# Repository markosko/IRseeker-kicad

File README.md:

View this project on [CADLAB.io](https://cadlab.io/project/27377).

# IRseeker-kicad

Used as replacement for IRseeker sensor and similar for Lightweight / Entry leagues with infra ball in Robocup Junior, based on STM32G431CBU6 and TSSP4038

With communication over I2C or Serial protocol.

Serial over **TX_3V** / **RX_3V** pins is **only 3.3V tolerant**!

Serial over **TX3_5V** / **RX3_5V** pins is **5V tolerant**.

**I2C** is 5V tolerant.

Logic **AND** gates **HEF4082BT** at **U2** and **U4** are optional for chip at PC6 pin input to detect if any TSSP4038 detects ball.

**AMS1117** part is not needed in case of powering from 3.3V source

Programmed by external STLINK or similar over SWD pins at J13 header.

[Basic serial code](https://github.com/markosko/IRseeker-stmduino-serial)

[Basic I2C code](https://github.com/markosko/IRseeker-stmduino-i2c)

# 3D view from KiCad

# Assembled images

# Sponsored by

<p align=center>
A big thanks to <a href="https://www.pcbway.com/">PCBway</a> for sponsoring my project! Their rapid-prototyping services provided top-quality PCB boards, streamlining the entire process from order to delivery. I was particularly impressed by their outstanding customer support, which was willing to change few details.
</p>

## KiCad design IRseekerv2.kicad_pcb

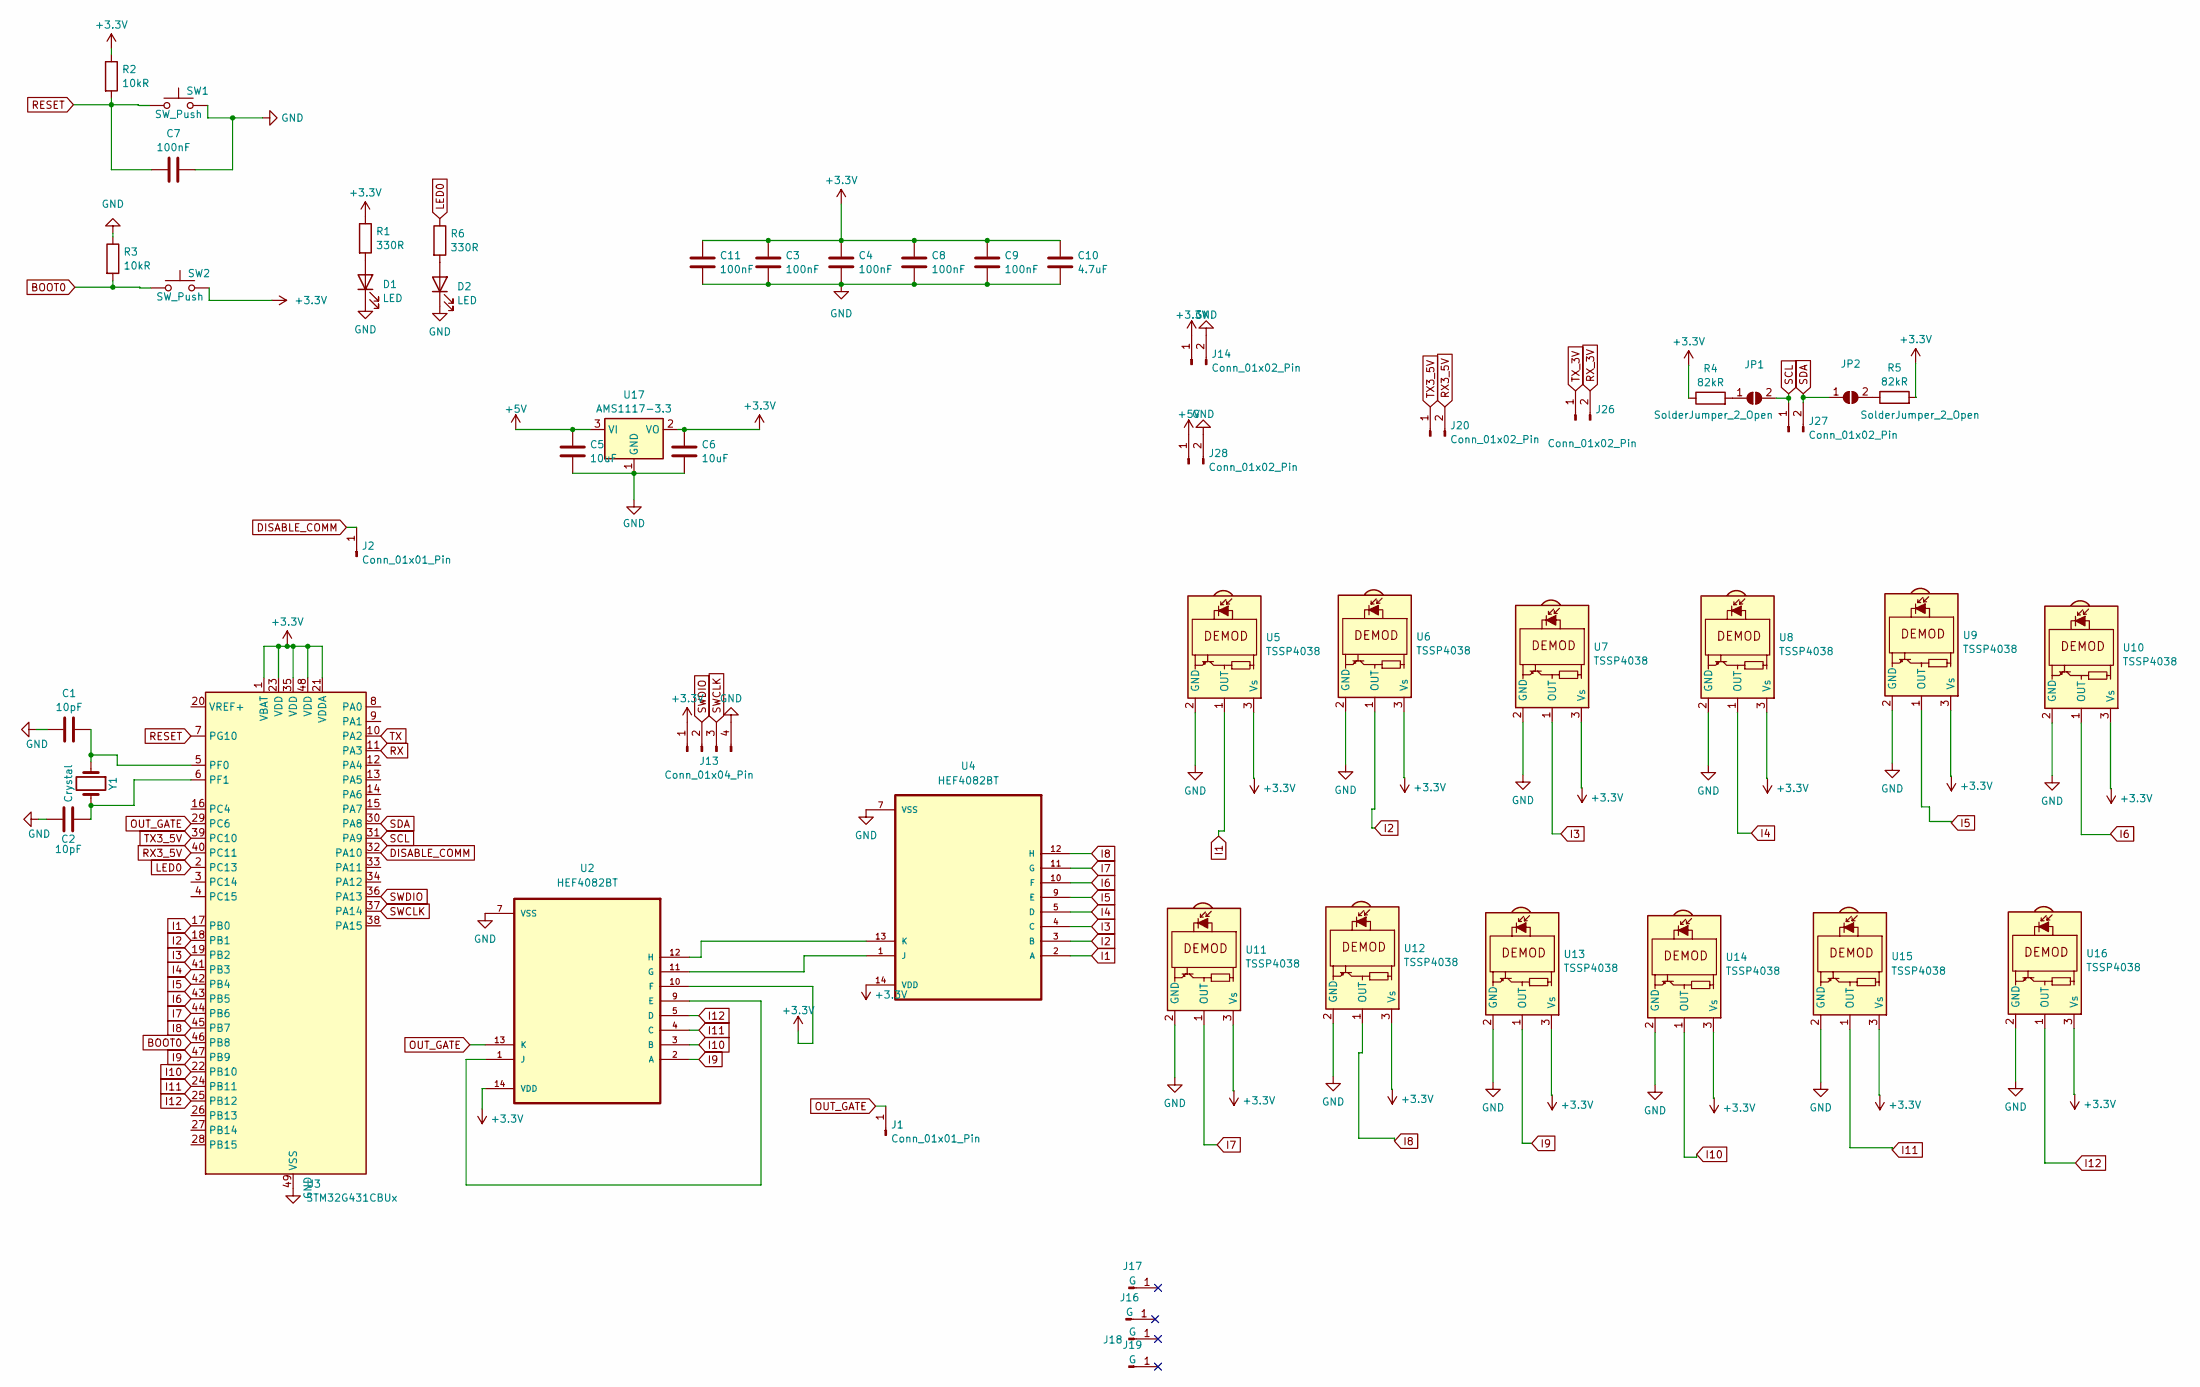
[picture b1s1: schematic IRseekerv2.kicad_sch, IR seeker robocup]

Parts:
C1, C2: 10pF; C_0603_1608Metric
C3, C4, C7, C8, C9, C11: 100nF; C_0603_1608Metric
C5, C6: 10uF; C_0603_1608Metric
C10: 4.7uF; C_0603_1608Metric
D1, D2: LED; LED_0603_1608Metric
J1, J2: Conn_01x01_Pin; PinHeader_1x01_P2.54mm_Vertical
J13: Conn_01x04_Pin; PinHeader_1x04_P2.54mm_Vertical
J14, J20, J26, J27, J28: Conn_01x02_Pin; PinHeader_1x02_P2.54mm_Vertical
J16, J17, J18, J19: G; MountingHole_3.2mm_M3_Pad
JP1, JP2: SolderJumper_2_Open; SolderJumper-2_P1.3mm_Open_TrianglePad1.0x1.5mm
R1, R6: 330R; R_0603_1608Metric
R2, R3: 10kR; R_0603_1608Metric
R4, R5: 82kR; R_0603_1608Metric
SW1, SW2: SW_Push; SW_PUSH_6mm
U2, U4: HEF4082BT; SO-14_3.9x8.65mm_P1.27mm
U3: STM32G431CBUx; QFN-48-1EP_7x7mm_P0.5mm_EP5.6x5.6mm
U5, U6, U7, U8, U9, U10, U11, U12, U13, U14, U15, U16: TSSP4038; Vishay_MINICAST-3Pin
U17: AMS1117-3.3; SOT-223-3_TabPin2
Y1: Crystal; Crystal_SMD_HC49-SD

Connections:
+3.3V: C3.2, C4.2, C6.2, C8.2, C9.2, C10.2, C11.2, J13.1, J14.1, R1.1, R2.1, R4.1, R5.2, SW2.2, U2.10 (F), U2.14 (VDD), U3.1 (VBAT), U3.21 (VDDA), U3.23 (VDD), U3.35 (VDD), U3.48 (VDD), U4.14 (VDD), U5.3 (Vs), U6.3 (Vs), U7.3 (Vs), U8.3 (Vs), U9.3 (Vs), U10.3 (Vs), U11.3 (Vs), U12.3 (Vs), U13.3 (Vs), U14.3 (Vs), U15.3 (Vs), U16.3 (Vs), U17.2 (VO)
+5V: C5.2, J28.1, U17.3 (VI)
BOOT0: R3.2, SW2.1, U3.46 (PB8)
DISABLE_COMM: J2.1, U3.32 (PA10)
GND: C1.1, C2.1, C3.1, C4.1, C5.1, C6.1, C7.1, C8.1, C9.1, C10.1, C11.1, D1.1 (K), D2.1 (K), J13.4, J14.2, J28.2, R3.1, SW1.2, U2.7 (VSS), U3.49 (VSS), U4.7 (VSS), U5.2 (GND), U6.2 (GND), U7.2 (GND), U8.2 (GND), U9.2 (GND), U10.2 (GND), U11.2 (GND), U12.2 (GND), U13.2 (GND), U14.2 (GND), U15.2 (GND), U16.2 (GND), U17.1 (GND)
I1: U3.17 (PB0), U4.2 (A), U5.1 (OUT)
I2: U3.18 (PB1), U4.3 (B), U6.1 (OUT)
I3: U3.19 (PB2), U4.4 (C), U7.1 (OUT)
I4: U3.41 (PB3), U4.5 (D), U8.1 (OUT)
I5: U3.42 (PB4), U4.9 (E), U9.1 (OUT)
I6: U3.43 (PB5), U4.10 (F), U10.1 (OUT)
I7: U3.44 (PB6), U4.11 (G), U11.1 (OUT)
I8: U3.45 (PB7), U4.12 (H), U12.1 (OUT)
I9: U2.2 (A), U3.47 (PB9), U13.1 (OUT)
I10: U2.3 (B), U3.22 (PB10), U14.1 (OUT)
I11: U2.4 (C), U3.24 (PB11), U15.1 (OUT)
I12: U2.5 (D), U3.25 (PB12), U16.1 (OUT)
LED0: R6.1, U3.2 (PC13)
unnamed: D1.2 (A), R1.2
unnamed: D2.2 (A), R6.2
unnamed: JP1.1 (A), R4.2
unnamed: JP2.2 (B), R5.1
unnamed: U2.1 (J), U2.9 (E)
unnamed: U2.11 (G), U4.1 (J)
unnamed: U2.12 (H), U4.13 (K)
unnamed: C1.2, U3.5 (PF0), Y1.1
unnamed: C2.2, U3.6 (PF1), Y1.2
OUT_GATE: J1.1, U2.13 (K), U3.29 (PC6)
RESET: C7.2, R2.2, SW1.1, U3.7 (PG10)
RX: U3.11 (PA3)
RX3_5V: J20.2, U3.40 (PC11)
RX_3V: J26.2
SCL: J27.1, JP1.2 (B), U3.31 (PA9)
SDA: J27.2, JP2.1 (A), U3.30 (PA8)
SWCLK: J13.3, U3.37 (PA14)
SWDIO: J13.2, U3.36 (PA13)
TX: U3.10 (PA2)
TX3_5V: J20.1, U3.39 (PC10)
TX_3V: J26.1

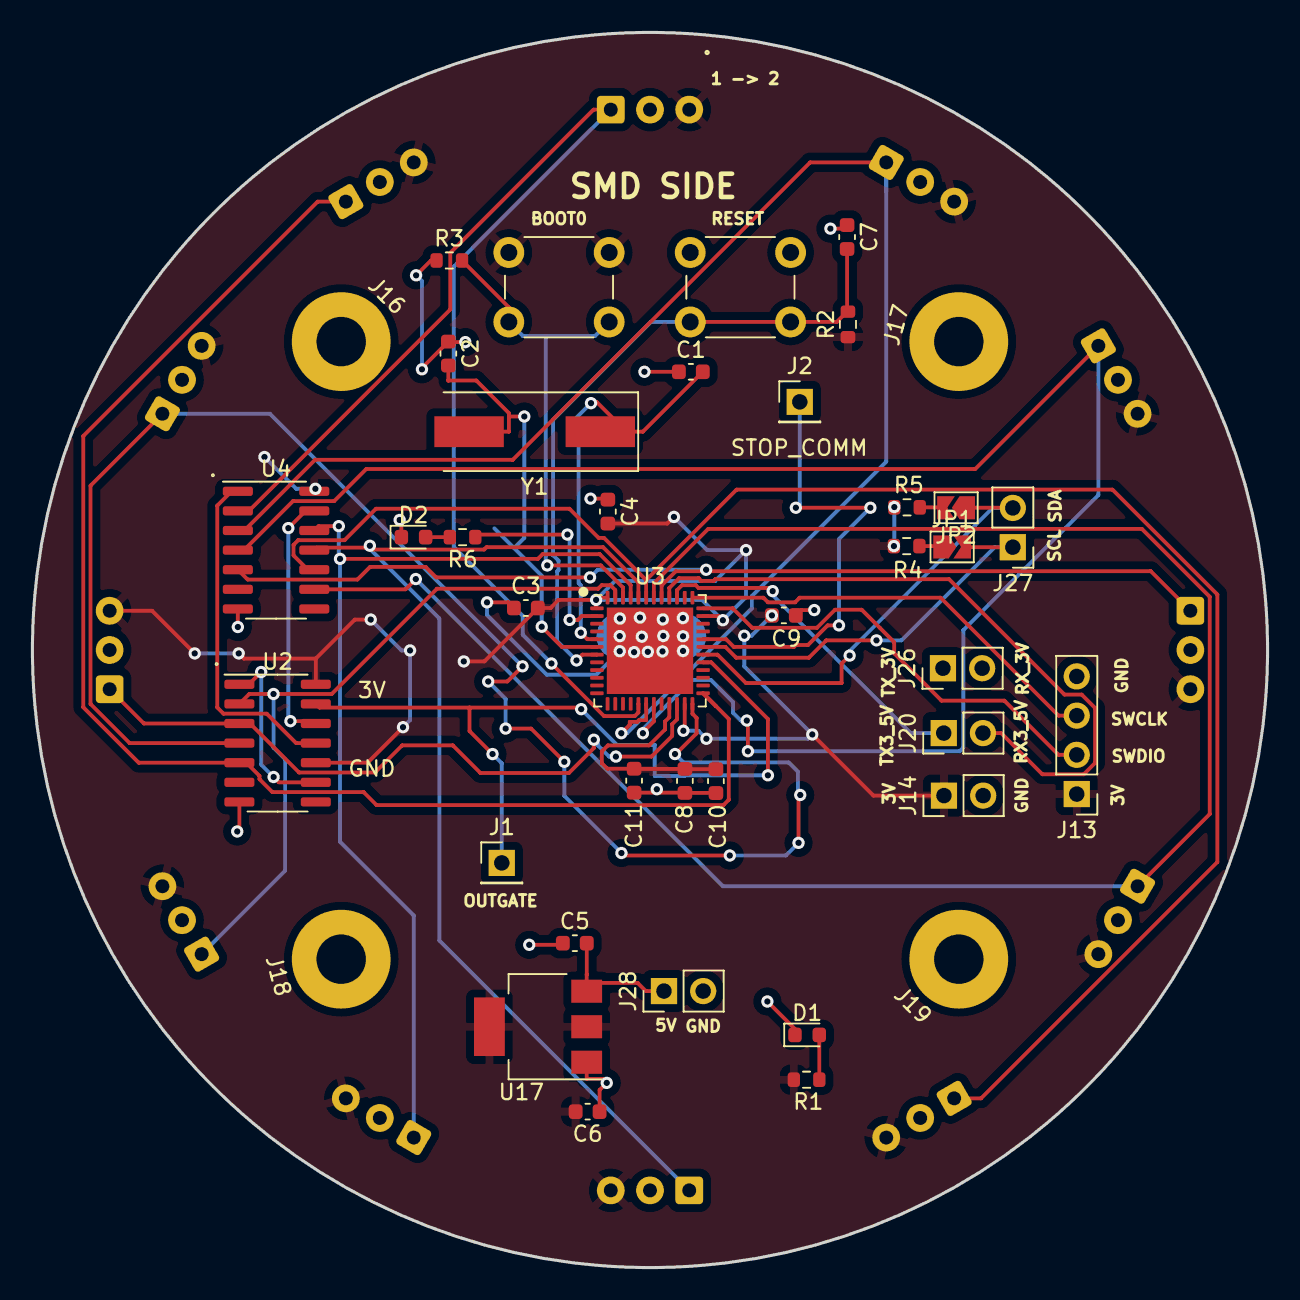
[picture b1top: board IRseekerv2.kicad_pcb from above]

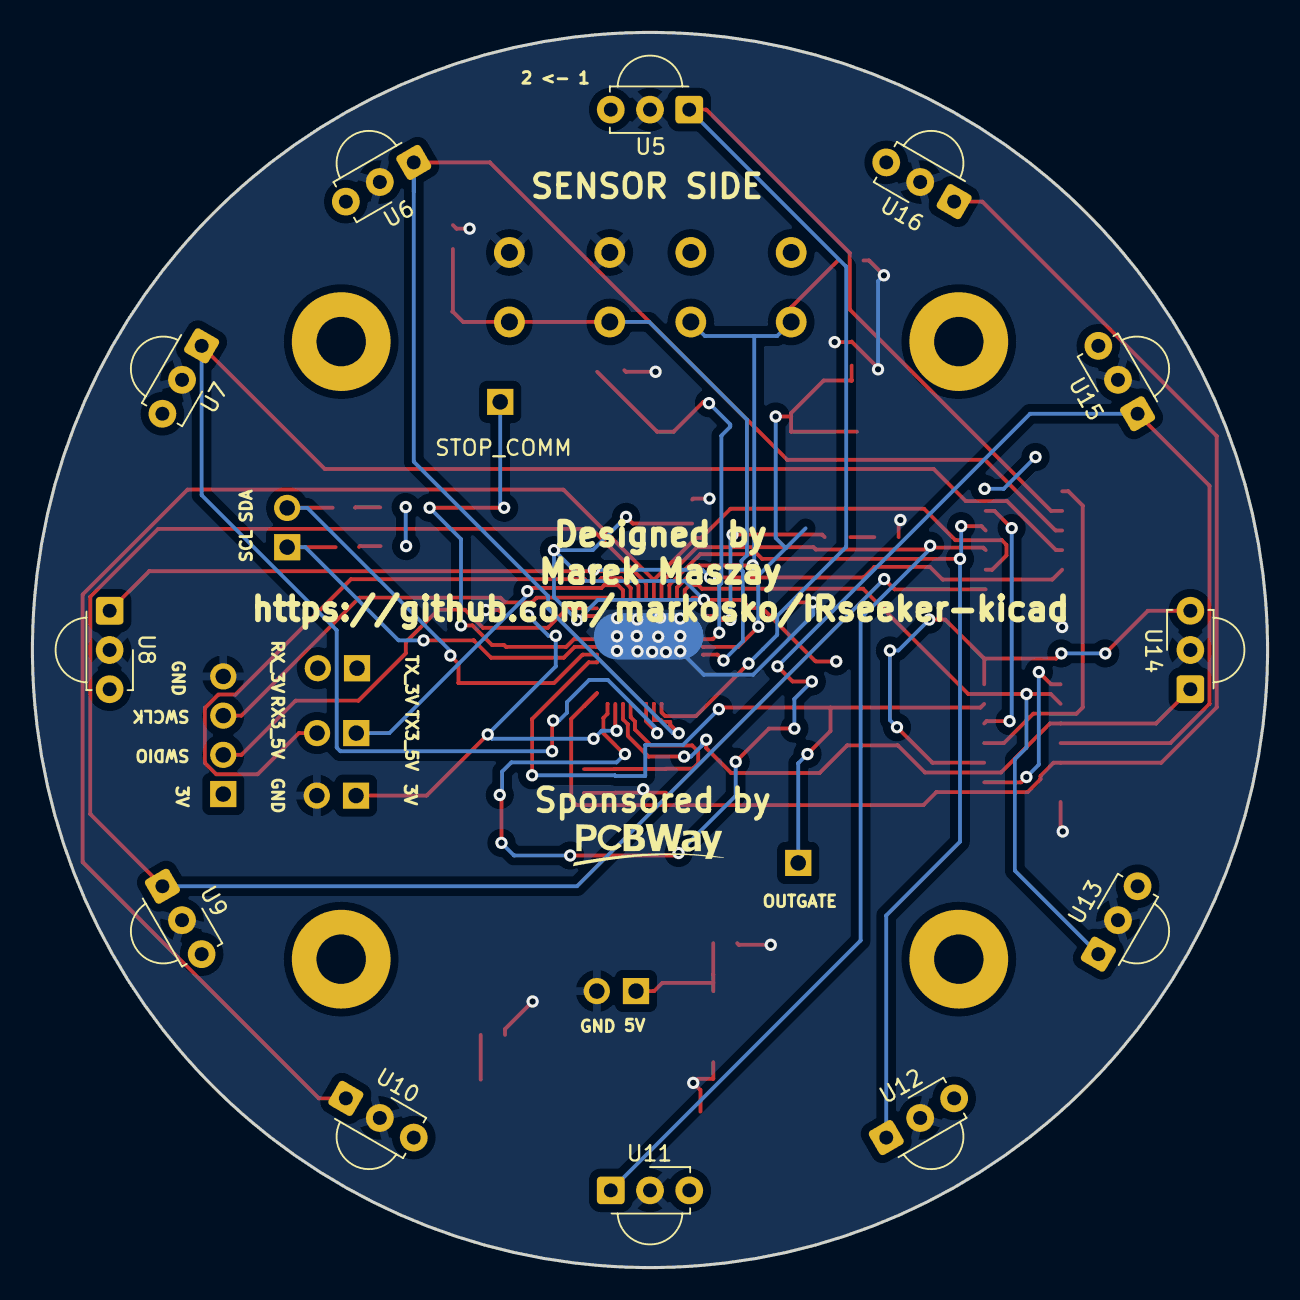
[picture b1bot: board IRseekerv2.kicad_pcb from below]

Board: 2 copper layers, 80.0 x 80.0 mm, 52 parts (12 on the bottom side), 35 nets.

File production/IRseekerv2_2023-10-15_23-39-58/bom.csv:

Designator,Footprint,Quantity,Value,LCSC Part #
"C1, C2",C_Disc_D3.0mm_W1.6mm_P2.50mm,2,10pF,
"C5, C6",C_Disc_D3.0mm_W1.6mm_P2.50mm,2,10uF,
C7,C_Disc_D3.0mm_W1.6mm_P2.50mm,1,100nF,
D1,LED_D3.0mm,1,LED,
J13,PinHeader_1x04_P2.54mm_Vertical,1,Conn_01x04_Pin,
"J14, J20, J26, J27, J28",PinHeader_1x02_P2.54mm_Vertical,5,Conn_01x02_Pin,
J15,PinHeader_1x03_P2.54mm_Vertical,1,SEL_VOLTAGE,
"J16, J17, J18, J19",MountingHole_3.2mm_M3_Pad,4,G,
J21,PinHeader_1x01_P2.54mm_Vertical,1,Conn_01x01_Female,
R1,R_Axial_DIN0204_L3.6mm_D1.6mm_P1.90mm_Vertical,1,330R,
"R2, R3",R_Axial_DIN0204_L3.6mm_D1.6mm_P1.90mm_Vertical,2,10kR,
"SW1, SW2",SW_PUSH_6mm,2,SW_Push,
"U10, U11, U12, U13, U14, U15, U16, U5, U6, U7, U8, U9",Vishay_MINICAST-3Pin,12,TSSP4038,
U17,SOT-223-3_TabPin2,1,AMS1117-3.3,
U2,DIP794W45P254L1969H508Q14,1,CD4012,
U3,QFN-48-1EP_7x7mm_P0.5mm_EP5.6x5.6mm,1,STM32G431CBUx,
U4,DIP794W45P254L1969H508Q14,1,CD4012B,
Y1,Crystal_HC49-4H_Vertical,1,Crystal,

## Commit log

2023-08-13 clean zips
2023-09-25 Backlink to CADLAB.io has been added.
2023-09-25 remove file
2023-10-15 reworked to put STM32G431CBU6 on board
2023-10-15 Writen more info in README and removed output jumper in PCB
2023-10-15 remove lock files
2023-10-15 add lck files to gitignore
2023-10-19 I2C pullup resistors
2023-10-19 Disconnected mounting holes from ground, reroute some connections because of I2C pullups
2023-10-19 Added label to bottom side
2023-10-21 New images and production files
2023-11-11 Add forgotten decoupling capacitors and change footprints
2023-11-11 Autosave
2023-11-11 save
2023-11-12 Reworked to some smd components
2023-12-25 update production and images to last version
2023-12-29 BOOT0 pulldown instead of pullup
2023-12-30 Added label for site and "designed by"
2023-12-30 change in README logic gate chip
2024-02-11 removed SEL_VOlTAGE and added OUTGATE pin out
2024-03-02 images
2024-03-02 change crystal to smd version
2024-03-02 add link to basic serial code
2024-03-05 link to I2C example repo code
2024-03-24 sponsorship text change
2024-03-24 STOP_COMM pin, solder pads for resistors on I2C lines
